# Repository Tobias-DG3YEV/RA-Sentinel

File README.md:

# Project RA-Sentinel - a Radio Access Sentinel
FPGA-based Radio Receiver for securing WiFi and other access points against hacking attacks.

RA-Sentinel is an open-source project focused on creating a cost-effective, small, and low-power wideband radio receiver device that employs an FPGA to automatically detect malicious attacks on WiFi access points, such as Man in the Middle and Denial of Service attacks. By monitoring any WiFi cell, the device enhances internet safety for everyday users.
The device features low-cost receive-only chips that digitize 40 MHz of the WiFi radio spectrum at 2.4 GHz. An FPGA extracts relevant properties from demodulated and decoded packets in real-time without storage. These properties are then processed by a neural network, also implemented on the FPGA, to determine if the traffic is genuine or an attack.

The project was later extended with a directional 4-channel RF front end (RASRF2400WBMC) that adds Angle of Arrival (AoA) estimation, see the Sub Projects section below.

## Funding
<p align="center">
  
  &nbsp;&nbsp;
  
</p>

**RA-Sentinel (main project)**

This project was funded through the [NGI0 Entrust](https://nlnet.nl/entrust) Fund, a fund established by [NLnet](https://nlnet.nl/) with financial support from the European Commission's [Next Generation Internet](https://ngi.eu/) programme, under the aegis of [DG Communications Networks, Content and Technology](https://commission.europa.eu/about-european-commission/departments-and-executive-agencies/communications-networks-content-and-technology_en) under grant agreement No 101069594.

**RASRF2400WBMC (directional / AoA extension)**

This sub-project was funded through the [NGI0 Commons Fund](https://nlnet.nl/commonsfund), a fund established by [NLnet](https://nlnet.nl/) with financial support from the European Commission's [Next Generation Internet](https://ngi.eu/) programme, under the aegis of [DG Communications Networks, Content and Technology](https://commission.europa.eu/about-european-commission/departments-and-executive-agencies/communications-networks-content-and-technology_en) under grant agreement No [101135429](https://cordis.europa.eu/project/id/101135429). Additional funding is made available by the [Swiss State Secretariat for Education, Research and Innovation](https://www.sbfi.admin.ch/sbfi/en/home.html) (SERI).

---

## Latest Updates 

| Date       | Change                                                                                                                                                                                          | Link                                                                                        |
| ---------- | ----------------------------------------------------------------------------------------------------------------------------------------------------------------------------------------------- | ------------------------------------------------------------------------------------------- |
| 2026-10-08 | Four-channel receiver: angle-of-arrival polar display, real-time phase comparison, IQ snapshot capture to a PC over gigabit Ethernet. FPGA1 now free of Xilinx IP (openCMUL, openCDIV, openFFT) | [/Documentation/iq_capture](./Documentation/iq_capture/README.md)                           |
| 2026-09-30 | RASBB Revision C manufacturing started                                                                                                                                                          |                                                                                             |
| 2026-07-24 | RASPMO - 4ch Spectrum Monitor/Phase analysis                                                                                                                                                    | [/RASPMO](./RASPMO)                                                                         |
| 2026-06-30 | RASANT2400 - 2.4 GHz antenna for RF front ends                                                                                                                                                  | [/RASANT2400](./RASANT2400)                                                                 |
| 2026-04-15 | RASRF2400WBMC - directional 4-channel RF front end for Angle-of-Arrival estimation                                                                                                              | [/RASRF2400WBMC](./RASRF2400WBMC/README.md)                                                 |
| 2025-12-15 | RASBB_ECU firmware - adds UPNP discovery over Ethernet and a system configuration web page                                                                                                      | [/RASBB/Software/RASBB_ECU](./RASBB/Software/RASBB_ECU)                                     |
| 2025-02-23 | First boards of RASBB and RASRF2400WB received; bring-up ongoing                                                                                                                                | [RASBB README](./RASBB/README.md) &nbsp;\|&nbsp; [Findings Rev A](./RASBB/Findings_RevA.md) |

---

## System Architecture

---
## Hardware

The hardware is a wideband SDR receiver that receives at least one complete WiFi Channel on the 2.4GHz ISM band with high resolution (12 Bits) to be able to detect smallest anomalies in a transmitted signal. The initial evaluation hardware consists of a Downcoverter/Transceiver Chip for 2.4GHz which is widely used in older WiFi Access Points (MAX2831). This is followed by a 12 Bit ADC (Texas Instruments ADC3222) which converts a 40MHz window of the 2.4GHZ radio spectrum into a 4 x 240 Bit/s LVDS streams (960kBit/s total) into a XILNIX/AMD Artix7 FPGA sitting on a evaluation board made by QMTECH. 

Based on the experience collected with first prototype, we designed a new SDR prototype. Two boards of the RASBB and the RASRF2400 have arrived on 23rd. Feb. 2025
Testing and bringing up is now ongoing. First results and findings can be found in the corresponding [Findings_RevA.md](./RASBB/Findings_RevA.md) documents.

### Boards

| Board | Description | Location |
|---|---|---|
| **RFFE2400WB** | 2.4 GHz PMOD-connected RF front-end evaluation board (used with QM-Tech Artix-7) | [/RFFE2400WB](./RFFE2400WB) |
| **RASBB** | Base-band board with STM32 ECU, web config, Ethernet/UPNP | [/RASBB](./RASBB) |
| **RASRF2400WB** | Wideband 2.4 GHz RF front end (production variant) | [/RASRF2400WB](./RASRF2400WB) |
| **RASRF2400WBMC** | Directional 4-channel phase-coherent front end (AoA) - *new sub-project* | [/RASRF2400WBMC](./RASRF2400WBMC) |
| **RASANT2400** | 2.4 GHz antenna for RF front ends| [/RASANT2400](./RASANT2400) |

*Picture 1: First RA-Sentinel prototype based on the QM-Tech Artix-7 board and a newly designed RF front end connected via PMOD.*

*Picture 2: RA-Sentinel prototype Revision A with RF front-end board RASRF2400WB.*

FPGA development board reference: <https://de.aliexpress.com/item/1005006473783593.html>

---

## Software / Firmware

The vast majority of the code will be written in Verilog and run on the FPGA. There is also now a firmware for the RASBB_ECU (Embedded Control Unit) and a"house keeping unit" microcontroller (STM32C031) which programms and controlling the frontend chips. The RASBB_ECU provides the interconnectivity. with other systems (alarm forwarding) and the web configuration interface. This firmware is written in C. 

The firmware for the RASBB_ECU can be found The firmware for the RASBB_ECU can be found [here](./RASBB/Software/RASBB_ECU). 

The RASBB_ECU Firmware for the onboard STM32 provides a versatile configuration interface with GUI that allows to show statistics and maybe UDP for analytic packets transfer and secure TCP/IP configuration over Ethernet.
To access this, enter the IP of the RAS into your local browser like http://192.168.0.2:4842/. The IP can be easily found via network environment because the RAS supports UPNP over ethernet.

All original software/firmware code written for this project is licensed under the GNU General Public License 3.0 (Only).

A suspected WiFi node can be

* Tracked: Monitored by relative signal strength and later with additional direction. These values are forwarded to an IDS host that can combine this information with additional data retrieved from different RAS or other network monitoring systems.
* Tagged: Marked for internal memory, moving up in watch list.
* Fingerprinted: Raw IQ data of the frame start is forwarded to a fingerprinting algorithm.

**UPNP support**

To ease the installation process, the RAS can be connected to any ethernet based LAN that provides an IPv4 DHCP server. Through the UPNP support, the RAS is easy to find in any network browser of Windows, Linux and Mac etc. 

---

## Sub Projects / Project Steps

The first step on this project was to have a reliable hardware basis. Initially I planned to have at least 40 Megasamples and with this 20 MHz bandwidth which is sufficient to capture the headers and the most common bandwidths used on 2.4 GHz WiFi (802.11a, b, g) communications channel. But because 802.11n also defines the possibility to use 40 MHz bandwidth, I wanted the possibility to cover the complete possible channel bandwidth. This has been achieved with the first prototype hardware and proved with the sub-project RASM2400, Radio Access Spectrum Monitor for 2400 MHz. The directional variant, RASRF2400WBMC, extends this base with multi-channel phase-coherent reception so the same signal can be received across several antennas and the direction of an attack can be estimated. You can find all sub-project details below.

### Sub project: RASRF2400WBMC - Directional RF Front End

The **RASRF2400WBMC** is a 4-channel, phase-coherent 2.4 GHz RF front-end board that extends RA-Sentinel with **Angle of Arrival (AoA)** estimation. By receiving the same signal across four spatially separated antennas, the system can estimate the physical direction of a detected attack - enabling threat localization for jamming, spoofing, and unauthorized events.

The board connects to the existing RASBB via the PCIe connector and requires no hardware changes to the base-band board.

See **[RASRF2400WBMC/README.md](./RASRF2400WBMC/README.md)** for full details.

### Sub project: RASM2400 - a spectrum monitor

RASM2400 stands for Radio Access Spectrum Monitor operationg on 2400MHZ. It offers a visual spectrum analyzer design that runs on the evaluation hardware set of RA-Sentinel the Artix7 XC7A100T Wukong board and the RFFE2400 front end board.
It shall proove that a 40MHz wide radio spectrum can be received and transported into the FPGA. Further, this project may already be usable for first RF forensics. Feel free to download all the stuff and build an RASM by yourself.

The following diagram shows the system architecture of the RASM2400.

The output of the HDMI port of the QMTECH Wukong board.

Watch a short demonstration on Youtube by clicking on the thumbnail below.

#### Software

In this repository you'll find also all software paerts needed to get the project up and running.

**/RASM2400_Verilog**

This folder contains the Verilog source files as well as a ready to program bit stream file. 

**/RASM2400_HKU**

Here you find the firmware for the RF board housekeeping unit. It does not do much a the moment but initializing the Downconverter MAX2831 and the ADC3222. It is planned to receive commands via I2C to change basic parameters wil center frequency, sensitivity and AGC characteristics. This project can be compiled with arm-gcc or with the free available and Eclipse based development environment (IDE) from ST called "STM32CubeIDE". You can download this IDE from ST.com [https://www.st.com/en/development-tools/stm32cubeide.html]

**/RASPMO**

Radio Access Spectrum Monitor with HDMI Output. A firmware project for the analog processing FPGA (U10).
THis shows all four spectra of all four channels of the RASRF2400BMC front end on the HDMI output at 1080p60 resolution. It also can overlay a polar indicator that gices an coarse indication where the signal is comming from. 

#### Project update 13th Oct. 2024

The target of the next Milestone #2 was the „Identification and isolation of appropriate software components“ and also to „Additionally apply modifications to the openOFDMmodule to get extra meta data out of the frame demodulator to have a wider data basis for the later fingerprinting process.“

In the following points I describe how I achieved each step of this Milestone.

**1. compile/synthesize openWiFi on the target FPGA**

The code of openWiFi has been successfully ported from the project GitHub site [1] to the evaluation setup that I have designed and set up in the first Milestone. After gluing together the ADC LVDS deserializer block inside the FPGA with the parallel input of the openOFDM core, got rid of several timing constraint issues, I finally achieved to decode a WiFi Frame coming from an arbitrary signal generator. To accomplish this target, the code needed to be isolated from the original open WiFi demo project code. This original demo was based on SDR evaluation boards relying all on the AMD ZYNQ FPGA-ARM chip family. This family provides an FPGA part and an integrated ARM micro processor to which all communication of the FPGA part is connected to. Data from and to the integrated processor is exchanged through a common memory bus. This however is not working with my design idea which is based on a more powerful FPGA with an external ARM co-processor. I tried extracting the needed HDL (Verilog) parts and make this code running stand-alone. Finally I came the conclusion that only the project „openOFDM“ needs to be ported to my RA-Sentinel project hardware because the network layer and the transmit part implemented in openWiFi is not really needed by the RA-Sentinel project because there is no need in routing real data back and forth to a network. We are only interested in the lowest layer of a WiFi frame and its analog characteristics, not the routing of packets and also not in the frame containing payload as such.

First I adapted the test-bench provided in [2] for the Vivado simulation environment. To be able to simulate the complete RA-Sentinel hardware, I created a LVDS emulator that can stream artificial synthesized and recorded  RF data coming originally from the TI ADC 3221. After providing recorded RF data via this LVDS simulator and generating a appropriate, to the ADC phase-locked master clock of 100MHz to the openOFDM core and (see top_tb.v), this setup was able to decode a complete 802.11a/g frame in the AMD Vivado simulator. It took me quite some fiddling and playing with timings and implementation settings of the tool-chain to finally get it running properly on my own hardware. (AMD Artix7 development board my QM-Tech and my 2.4GHz ADC board designed in Milestone 1)

**2. Strip down openWiFi and open OFDM to the receive part**

First this was regarded as an easy task but as deeper I dived into the code  by the original author of the two projects, the more I realized the code provides almost no comments and wire and register definitions are quite ambiguous and non-intuitive. In my opinion the code needed desperately a rework to be better understandable which would also lead to a lower learning curve for others also trying to implement and adapt the existing code base to their needs. Two major things I tried improving with my fork of openOFDM: The introduction of directional prefixes for module ports. I have seen such in the code of another NLnet founded guy called Dan Nissselquist. Adding the prefix  „i_“ to  input ports (defined as wires/registers in Verilog) and „o_“ to the port definition makes it IMHO much easier when browsing through the code, allowing to instantly realize which wire or register is being exported from this current module and which is only a local element. I added these prefixes all over the code of openOFDM. See my fork of openOFDM on GitHub [1] for details. The next thing I found hard to understand, was the use of the ever repeating word „sample“ for all data along the signal path, from the input of the openOFDM core (ADC base-band data) up to near the exit (decoded data bytes). As there is a switch from time domain (endless sample stream) into frequency domain (blocks of 64 frequency bands) in the module „sync_long“, I changed the name of all wires and registers after this module and renamed them into „spectrum“.  Also some comments were added to clarify what a wire or register is doing at a certain point. This work is not yet regarded as being completed. Each time I dig into the original code, I will add comments and try to make the code more „barrier free“.

**3. Create a new fork of openOFDM**

This has been done and the new fork of openOFDm can be found here:

[1] https://github.com/Tobias-DG3YEV/openofdm

It contains comments and my code changes proposed earlier in this document.

**4. Try adding additional meta date stubs**

As I tried figuring out which meta data could be used to distinguish between  genuine transmitting device and a counterfeit device, I found an article at mathworks.com [3] reporting that they proved finding counterfeit, evil twins of a WiFi Access Point by feeding the raw sampled channel data of a transmission into a ML algorithm. For this purpose they followed a kind of a brute force approach by taking all samples of a received frame into account and fed into a ML algorithm. Even the smallest frame like an information or flow control frame that is only 100uS of duration will produce 16kBytes of data which is rather huge. This amount of data may be processable - if the SDR is directly connected to a powerful computer with multiple cores etc. The project RA-Sentinel does not follow this kind of big processing power approach. Amplitude, phase and frequency change due to several effects during the transmission of a frame, but all of these changes always result in a phase shift. So I thought, in  the first attempt identifying a WiFi transmitting device by characterizing (or say learning) the phase deviation over time may be sufficient. Because the RF receiver front end of the RA-Sentinel project has a low noise and high stability master clock (a 40MHz TXCO by Abracom) that is multiple times more accurate that standard commercial WiFi transmitters, I hope that a small amount of phase shift data received in the beginning of a WiFi frame may be enough to clearly identify counterfeit devices. 

**5. Redefine a new simplified interface to access meta parameters**

One thing I have learned throughout the project progress so far, is that even many may say that an FPGA is one of the most versatile digital programmable devices available today, allowing the implementation of any kind of parallel and sequential tasks up to integration of soft-core processors the fact is that all this integrated logic leads to a rather time consuming iterative development process. To optimize WiFi data reception on one side and to interpret and forward meta data on the other side all inside the FPGA leads to an extremely slow and challenging development process. For the analysis of meta data, an external, traditional single chip microprocessor running straight C/C++ code,  offers much more opportunities and most importantly, allows much a faster  development progress. Bit for that, I need a fast and reliable interconnection between the FPGA and the micro processor.

I identified and implemented two interfaces which allow to access 

The first interface I implemented into the FPGA was the SPI slave interface. This interface allows reading and writing 32 wide registers inside the FPGA by an external micro controller (in this case, I use a STM32H743 Cortex-M7)

The SPI interface allows access to the following parameters:

- Receiver characteristics like receiver center frequency, gain, power threshold, max. error rate etc.

- reading current receiver parameters like noise level, signal to noise ratio etc.

Further I needed an interface that is capable transferring header and  metadata that is produced with each WiFi 802.11 frame received to my  external ARM processor. As I cannot foresee at this point in the project how much meta data is needed to distinctly identify a sender hardware of a frame, I was looking for a method to reliably transport greater chunks of data from the FPGA directly into the memory of the external micro-controller without code intervention. Hence, I started evaluating the possibilities based on the peripheral capabilities of the STM32 device family.  After I had invested some effort into research and experiments, I found that SPI especially in a 4-Bit configuration might feasible as it is able transporting 25MByte/s. But the digital camera interface (DCMI) that many of those top range micro-controllers provide, offer 8 Bit parallel data transfer directly into the controller’s memory via DMA at a maximum rate of 80MBytes/s.

So the next step was to design a logic circuit into the FPGA that can mimic the signaling of a digital camera module with DCMI interface. This has been implemented on both sides, the FPGA in Verilog Code and on the STM32H7 in C language. 

The received 802.11 frame info packet that is streamed upon each complete frame reception has the following format:

---

**Resources:**

[1] https://github.com/open-sdr/openWiFi-hw/

[2] https://github.com/Tobias-DG3YEV/openofdm

[3] https://de.mathworks.com/help/comm/ug/design-a-deep-neural-network-with-simulated-data-to-detect-wlan-router-impersonation.html

Project Maintainer: Tobias Weber, Mina Daneshpajouh

Last updated: 17. May. 2026

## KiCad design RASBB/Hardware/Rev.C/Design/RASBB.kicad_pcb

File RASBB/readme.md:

# RA-Sentinel System Overview

The **RA-Sentinel** system consists of two main boards that work together to enable high-performance RF signal reception, digitization, and processing.

## RA-Sentinel Radio Front-End Board (RASRF)
The **RASRF** board is responsible for receiving and conditioning, and digitizing RF signals before transmitting them to the baseband processor.
 - The antenna is connected through a Balun to an RF front-end transceiver, which performs signal reception, downconversion, and filtering.
 - The downconverted signal is then conditioned using a driver circuit optimized for impedance matching and signal integrity.
 - A high-speed 12-bit ADC samples a 40 MHz portion of the 2.4 GHz radio spectrum, converting it into a 960 Mbit/s data stream (2 channels: I+Q, 12-bit each @ 40 
   MSPS). 
 - The digitized data is transmitted over a PCIe interface to the RASBB board for baseband processing.

## RA-Sentinel Baseband Board (RASBB)
The **RASBB** board processes the received digital RF data and manages higher-layer communication.
 - It performs baseband signal processing, extracting relevant information from the digitized RF data.
 - It transitions the processed data from OSI Layer 1 (Physical) to OSI Layer 2 (Data Link) for further communication and protocol handling.
 - The board integrates additional processing units and interfaces for system-level control, data management, and external communication.

Together, the **RASRF** and **RASBB** boards create a scalable, high-performance platform for RF signal acquisition and real-time processing.

Below is the block diagram illustrating the architecture of both boards and their interconnections:

## The hardware

The PCB of the RASBB is made of an FR4 eight-layer PCB, which contains several processing units, sensors, and radio and wired interfaces.
Below is an list of its features:

- Two Artix-7 FPGAs with 100k Logic Elements each
- 4 Gigabit (512MB with 16-bit access) Low Voltage DDR3 RAM
- STM32H7 high-performance (up to 480MHz) ARM Cortex-M7 microcontroller
- x8 PCI Express slot, designed to be compatible with PCI standards
- HDMI port, with video generated in FPGA 1
- 40-bit (32+8) inter-processor communication bridge (accessible by external logic analyzers)
- Two separately usable 16M Flash chips for FPGA configuration, accessible by both FPGA and STM32
- Temperature and humidity sensor for physical environment supervision
- Audio DAC with a 1W output amplifier (for alarm and voice output)
- Audio ADC for capacitive microphone connection (for acoustic environment surveillance)
- Open-collector 30V/1A capable switching output (for alarming devices)
- USB-C port with virtual COM port support for debugging and updates
- 2.4GHz LoRaWAN™ modem chip for robust alarm distribution
- 100Mbit/s Ethernet port connected to the STM32H7 MCU
- 1Gbit/s Ethernet port connected to FPGA 2
- Power over Ethernet (PoE) Type 1 with a maximum power of 13W
- LEDs for indication
- Configuration button
- FPGAs and STM32 accessible through JTAG port

*The RA-Sentinel Baseband Board design will fit into a 100mm extrusion enclosure. Hardware designed by **Mina Daneshpajouh**.*

RASBB Rev A (Top View)

RASBB Rev B (Bottom View)

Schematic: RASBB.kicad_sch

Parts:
C1, C2: 1uF; C_0402_1005Metric; Mfr. Part # 0402X105M160CT; LCSC Part # C3889771
C270: 100nF; C_0402_1005Metric; Mfr. Part # 0402B104K500CT; LCSC Part # C152814
C271, C272: 2200pF; C_0402_1005Metric; Mfr. Part # 0402B222K500NT; LCSC Part # C1531
J20: PWM_DAC_OUT; PinHeader_1x02_P2.54mm_Vertical; Mfr. Part # PZ254V-11-02P; LCSC Part # C492401
R1, R2, R3, R4, R6, R7, R8, R11, R12, R13, R14, R15, R16, R22: 49.9; R_0402_1005Metric; Mfr. Part # RMCF0402FT49R9; LCSC Part # C4229190
R9, R10: 4K7; R_0402_1005Metric; Mfr. Part # WR04X4701FTL; LCSC Part # C163826
R17, R18, R19, R20, R23, R24: 22; R_0402_1005Metric; Mfr. Part # WR04X22R0FTL; LCSC Part # C163821
R21, R168, R169, R170, R171, R172, R173, R174, R175, R176, R177, R178, R179, R180, R181, R182, R183, R184: 100; R_0402_1005Metric; Mfr. Part # WR04X1000FTL; LCSC Part # C163808
R150: 0; R_0603_1608Metric; Mfr. Part # RC0603JR-070RL; LCSC Part # C95177
R151, R195, R200, R201: 10K; R_0603_1608Metric; Mfr. Part # 0603WAF1002T5E; LCSC Part # C25804
SW1, SW2: 435451019820; Mfr. Part # 435451019820
TP6, TP7, TP8, TP9, TP10, TP11, TP12, TP13, TP14, TP15, TP16, TP17, TP18, TP19, TP20, TP21, TP22: TestPoint; TestPoint_Pad_D1.0mm; not fitted
U5: TLV9001DBVR; SOT-23-5; Mfr. Part # TLV9001QDBVRQ1; LCSC Part # C19632595

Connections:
/Audio_IN-OUT/3V3: C270.1, R9.2, R10.2, R200.2, R201.2, U5.5 (V+); also elsewhere on the board
/Audio_IN-OUT/Audio_IN: R21.2; also elsewhere on the board
/Audio_IN-OUT/LM386_INP: C2.2; also elsewhere on the board
/CS_FLASH_uC: TP18.1 (1_1); also elsewhere on the board
/Config-SPI FLASH/MUX_EN1: TP19.1 (1_1); also elsewhere on the board
/Config-SPI FLASH/MUX_EN2: TP20.1 (1_1); also elsewhere on the board
/Config-SPI FLASH/SCK_FLASH_FPGA2: R6.1; also elsewhere on the board
/Config-SPI FLASH/SCK_Flash_FPGA1: R1.2; also elsewhere on the board
/Config-SPI FLASH/SI_FLASH_FPGA2: R7.1; also elsewhere on the board
/Config-SPI FLASH/SI_Flash_FPGA1: R2.2; also elsewhere on the board
/Config-SPI FLASH/SO_FLASH_FPGA2: R8.1; also elsewhere on the board
/Config-SPI FLASH/SO_Flash_FPGA1: R4.2; also elsewhere on the board
/Config-SPI FLASH/SWITCH_FLASH_1: TP22.1 (1_1); also elsewhere on the board
/Config-SPI FLASH/SWITCH_FLASH_2: TP21.1 (1_1); also elsewhere on the board
/Ethernet_uC/RMII_CRS_DV: R20.1; also elsewhere on the board
/Ethernet_uC/RMII_REFCLK: R18.1; also elsewhere on the board
/Ethernet_uC/RMII_RXD0: R23.1; also elsewhere on the board
/Ethernet_uC/RMII_RXD1: R24.1; also elsewhere on the board
/Ethernet_uC/RMII_TXD0: R19.1; also elsewhere on the board
/Ethernet_uC/RMII_TXD1: R17.1; also elsewhere on the board
/FPGA1_RESET: SW1.4; also elsewhere on the board
/FPGA2_RESET: SW2.4; also elsewhere on the board
/FPGA-01/FPGA1_CLK: R1.1; also elsewhere on the board
/FPGA-01/FPGA1_MISO: R4.1; also elsewhere on the board
/FPGA-01/FPGA1_MOSI: R2.1; also elsewhere on the board
/FPGA-02/F2_B35_J2: R195.1; also elsewhere on the board
/PCIE/PCIE_MISO: R12.1; also elsewhere on the board
/PCIE/PCIE_MOSI: R3.1; also elsewhere on the board
/PCIE/PCIE_SCK: R11.1; also elsewhere on the board
/PCIE/RX0_N: R168.1; also elsewhere on the board
/PCIE/RX0_P: R168.2; also elsewhere on the board
/PCIE/RX1_N: R169.1; also elsewhere on the board
/PCIE/RX1_P: R169.2; also elsewhere on the board
/PCIE/RX2_N: R170.1; also elsewhere on the board
/PCIE/RX2_P: R170.2; also elsewhere on the board
/PCIE/RX3_N: R171.1; also elsewhere on the board
/PCIE/RX3_P: R171.2; also elsewhere on the board
/PCIE/RX4_N: R172.1; also elsewhere on the board
/PCIE/RX4_P: R172.2; also elsewhere on the board
/PCIE/RX5_N: R173.1; also elsewhere on the board
/PCIE/RX5_P: R173.2; also elsewhere on the board
/PCIE/RX6_N: R174.1; also elsewhere on the board
/PCIE/RX6_P: R174.2; also elsewhere on the board
/PCIE/RX7_N: R175.1; also elsewhere on the board
/PCIE/RX7_P: R175.2; also elsewhere on the board
/PCIE/RX8_N: R176.1; also elsewhere on the board
/PCIE/RX8_P: R176.2; also elsewhere on the board
/PCIE/RX9_N: R177.1; also elsewhere on the board
/PCIE/RX9_P: R177.2; also elsewhere on the board
/PCIE/RX10_N: R178.1; also elsewhere on the board
/PCIE/RX10_P: R178.2; also elsewhere on the board
/PCIE/RX11_N: R179.1; also elsewhere on the board
/PCIE/RX11_P: R179.2; also elsewhere on the board
/PCIE/RX12_N: R180.1; also elsewhere on the board
/PCIE/RX12_P: R180.2; also elsewhere on the board
/PCIE/RX13_N: R181.1; also elsewhere on the board
/PCIE/RX13_P: R181.2; also elsewhere on the board
/PCIE/RX14_N: R182.1; also elsewhere on the board
/PCIE/RX14_P: R182.2; also elsewhere on the board
/PCIE/RX15_N: R183.1; also elsewhere on the board
/PCIE/RX15_P: R183.2; also elsewhere on the board
/PCIE/RX16_N: R184.1; also elsewhere on the board
/PCIE/RX16_P: R184.2; also elsewhere on the board
/PCIE/SMCLK: R10.1; also elsewhere on the board
/PCIE/SMDAT: R9.1; also elsewhere on the board
/RF_Transceiver/BUSY_LORA_G: TP13.1 (1_1); also elsewhere on the board
/RF_Transceiver/DIO1_LORA_G: TP12.1 (1_1); also elsewhere on the board
/RF_Transceiver/DIO2_LORA_G: TP11.1 (1_1); also elsewhere on the board
/RF_Transceiver/DIO3_LORA_G: TP10.1 (1_1); also elsewhere on the board
/RF_Transceiver/NRST_LORA_G: TP14.1 (1_1); also elsewhere on the board
/RF_Transceiver/SPI_MISO_LORA_G: R22.2; also elsewhere on the board
/RF_Transceiver/SPI_MOSI_LORA_G: R16.2, TP7.1 (1_1); also elsewhere on the board
/RF_Transceiver/SPI_NSS_LORA_G: TP9.1 (1_1); also elsewhere on the board
/RF_Transceiver/SPI_SCK_LORA_G: R15.2, TP8.1 (1_1); also elsewhere on the board
/SCK_FLASH_FPGA2: R6.2; also elsewhere on the board
/SCK_FLASH_uC: R13.1, TP17.1 (1_1); also elsewhere on the board
/SI_FLASH_FPGA2: R7.2; also elsewhere on the board
/SI_FLASH_uC: R14.1, TP16.1 (1_1); also elsewhere on the board
/SO_FLASH_FPGA2: R8.2; also elsewhere on the board
/SO_FLASH_uC: TP15.1 (1_1); also elsewhere on the board
/uController/ADC1_IN5: C1.1; also elsewhere on the board
/uController/uC_DAC2_OUT2: C2.1; also elsewhere on the board
/uController/uC_ETH_CRS_DV: R20.2; also elsewhere on the board
/uController/uC_ETH_REF_CLK: R18.2; also elsewhere on the board
/uController/uC_ETH_RXD0: R23.2; also elsewhere on the board
/uController/uC_ETH_RXD1: R24.2; also elsewhere on the board
/uController/uC_ETH_TXD0: R19.2; also elsewhere on the board
/uController/uC_ETH_TXD1: R17.2; also elsewhere on the board
/uController/uC_SPI2_MISO: R22.1, TP6.1 (1_1); also elsewhere on the board
/uController/uC_SPI2_MOSI: R16.1; also elsewhere on the board
/uController/uC_SPI2_SCK: R15.1; also elsewhere on the board
/uController/uC_SPI3_MISO: R3.2; also elsewhere on the board
/uController/uC_SPI3_MOSI: R12.2; also elsewhere on the board
/uController/uC_SPI3_SCK: R11.2; also elsewhere on the board
/uController/uC_SPI4_MOSI: R14.2; also elsewhere on the board
/uController/uC_SPI4_SCK: R13.2; also elsewhere on the board
GND: C270.2, C271.2, C272.2, J20.1, SW1.2, SW1.3, SW1.5 (GND), SW2.2, SW2.3, SW2.5 (GND), U5.2 (V-); also elsewhere on the board
unnamed: C1.2, R21.1
unnamed: C272.1, R151.2, R195.2
unnamed: J20.2, R150.1
unnamed: R200.1, SW1.1
unnamed: R201.1, SW2.1
unnamed: C271.1, R151.1, U5.3 (+)
unnamed: R150.2, U5.1, U5.4 (-)

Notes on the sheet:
f3dB:5Hz

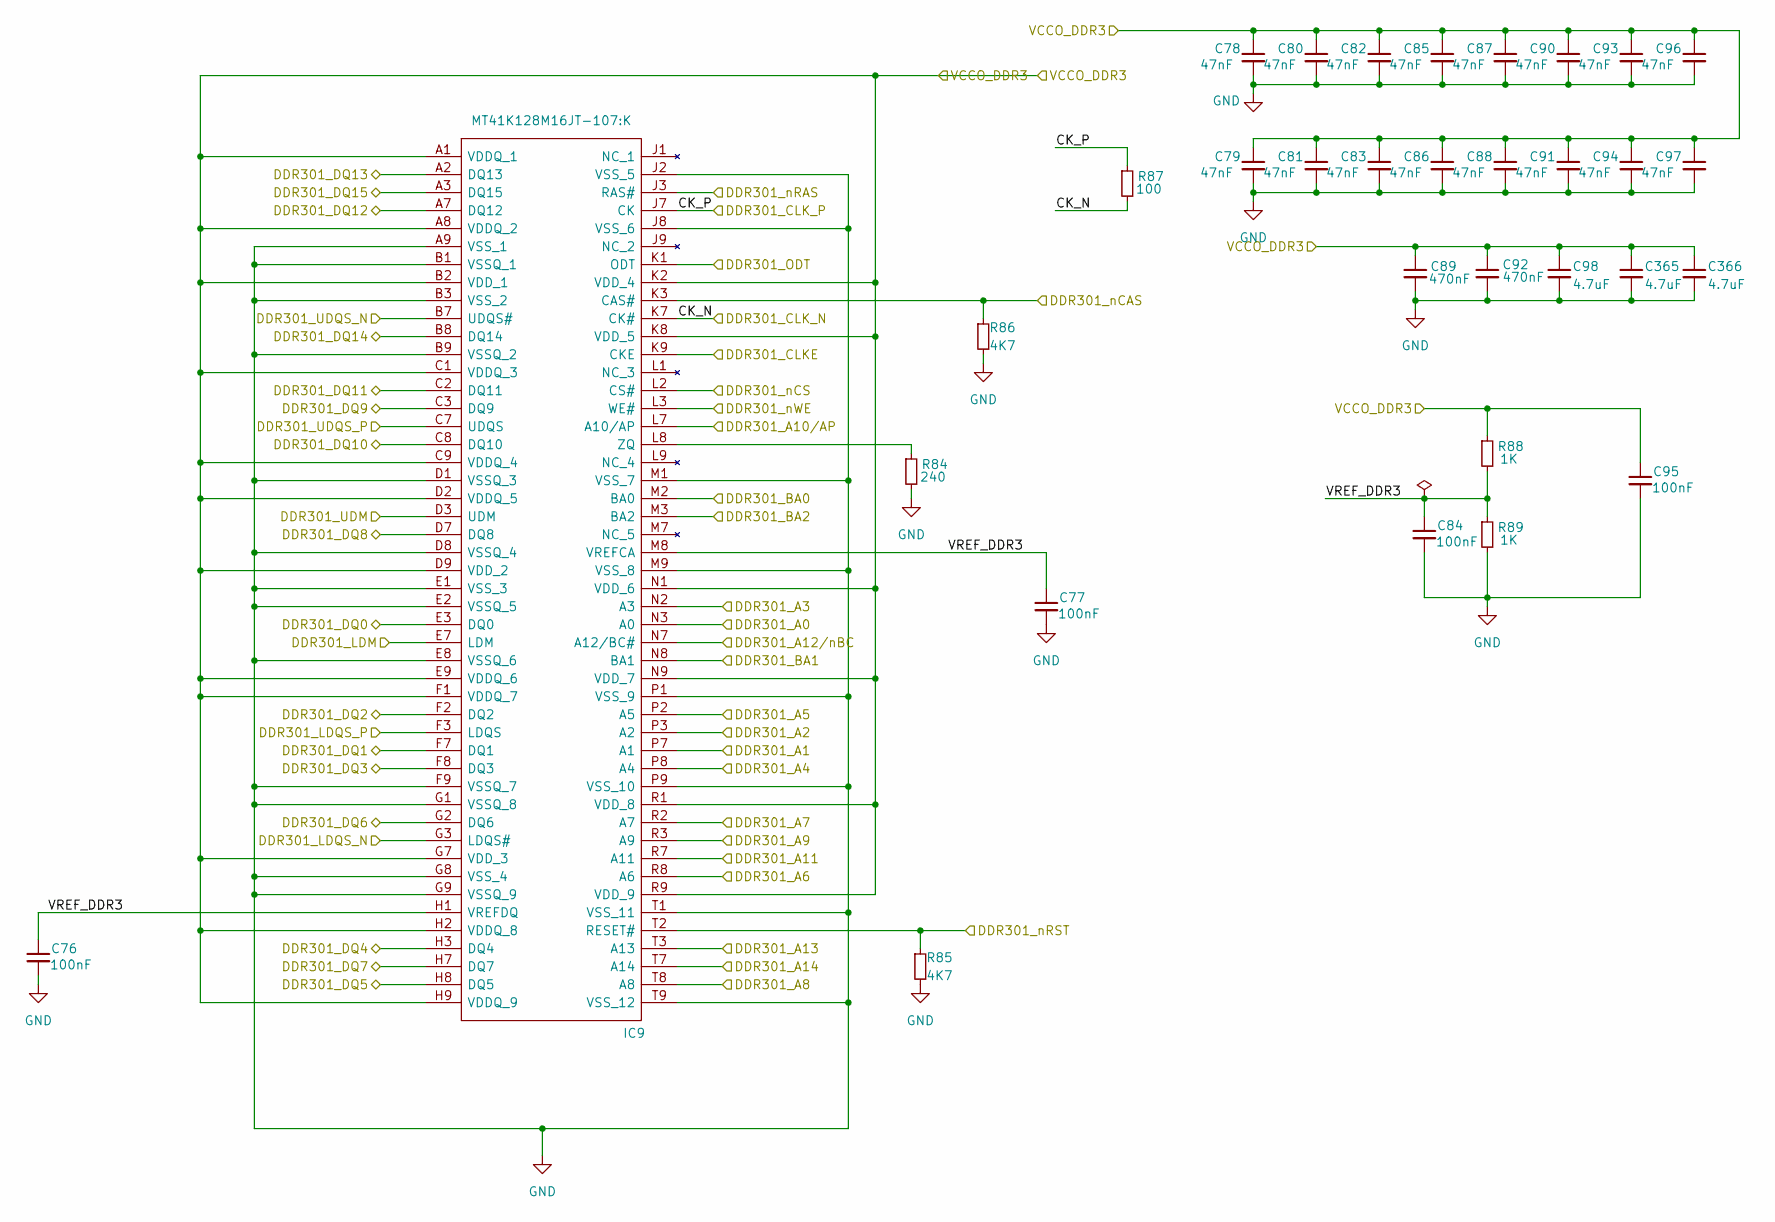
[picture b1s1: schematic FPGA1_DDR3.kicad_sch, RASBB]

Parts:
C76, C77, C84, C95: 100nF; C_0402_1005Metric; Mfr. Part # 0402B104K500CT; LCSC Part # C152814
C78, C79, C80, C81, C82, C83, C85, C86, C87, C88, C90, C91, C93, C94, C96, C97: 47nF; C_0402_1005Metric; Mfr. Part # C0402C473J8RAC7867; LCSC Part # C2178375
C89, C92: 470nF; C_0402_1005Metric; Mfr. Part # GRM155R71C474KE01D; LCSC Part # C471404
C98, C365, C366: 4.7uF; C_0603_1608Metric; Mfr. Part # GMK107BBJ475KA-T; LCSC Part # C7281848
IC9: MT41K128M16JT-107:K; BGA96C80P9X16_800X1400X120; Mfr. Part # MT41K128M16JT-107:K; LCSC Part # C2841151
R84: 240; R_0402_1005Metric; Mfr. Part # RT0402BRE07240RL; LCSC Part # C728568
R85, R86: 4K7; R_0402_1005Metric; Mfr. Part # WR04X4701FTL; LCSC Part # C163826
R87: 100; R_0402_1005Metric; Mfr. Part # WR04X1000FTL; LCSC Part # C163808
R88, R89: 1K; R_0402_1005Metric; Mfr. Part # MR04X1001FTL; LCSC Part # C327796

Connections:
/DDR3-01/CK_N: IC9.K7 (CK#), R87.2; also elsewhere on the board
/DDR3-01/CK_P: IC9.J7 (CK), R87.1; also elsewhere on the board
/DDR3-01/DDR301_A0: IC9.N3 (A0); also elsewhere on the board
/DDR3-01/DDR301_A1: IC9.P7 (A1); also elsewhere on the board
/DDR3-01/DDR301_A2: IC9.P3 (A2); also elsewhere on the board
/DDR3-01/DDR301_A3: IC9.N2 (A3); also elsewhere on the board
/DDR3-01/DDR301_A4: IC9.P8 (A4); also elsewhere on the board
/DDR3-01/DDR301_A5: IC9.P2 (A5); also elsewhere on the board
/DDR3-01/DDR301_A6: IC9.R8 (A6); also elsewhere on the board
/DDR3-01/DDR301_A7: IC9.R2 (A7); also elsewhere on the board
/DDR3-01/DDR301_A8: IC9.T8 (A8); also elsewhere on the board
/DDR3-01/DDR301_A9: IC9.R3 (A9); also elsewhere on the board
/DDR3-01/DDR301_A10/AP: IC9.L7 (A10/AP); also elsewhere on the board
/DDR3-01/DDR301_A11: IC9.R7 (A11); also elsewhere on the board
/DDR3-01/DDR301_A12/nBC: IC9.N7 (A12/BC#); also elsewhere on the board
/DDR3-01/DDR301_A13: IC9.T3 (A13); also elsewhere on the board
/DDR3-01/DDR301_A14: IC9.T7 (A14); also elsewhere on the board
/DDR3-01/DDR301_BA0: IC9.M2 (BA0); also elsewhere on the board
/DDR3-01/DDR301_BA1: IC9.N8 (BA1); also elsewhere on the board
/DDR3-01/DDR301_BA2: IC9.M3 (BA2); also elsewhere on the board
/DDR3-01/DDR301_CLKE: IC9.K9 (CKE); also elsewhere on the board
/DDR3-01/DDR301_DQ0: IC9.E3 (DQ0); also elsewhere on the board
/DDR3-01/DDR301_DQ1: IC9.F7 (DQ1); also elsewhere on the board
/DDR3-01/DDR301_DQ2: IC9.F2 (DQ2); also elsewhere on the board
/DDR3-01/DDR301_DQ3: IC9.F8 (DQ3); also elsewhere on the board
/DDR3-01/DDR301_DQ4: IC9.H3 (DQ4); also elsewhere on the board
/DDR3-01/DDR301_DQ5: IC9.H8 (DQ5); also elsewhere on the board
/DDR3-01/DDR301_DQ6: IC9.G2 (DQ6); also elsewhere on the board
/DDR3-01/DDR301_DQ7: IC9.H7 (DQ7); also elsewhere on the board
/DDR3-01/DDR301_DQ8: IC9.D7 (DQ8); also elsewhere on the board
/DDR3-01/DDR301_DQ9: IC9.C3 (DQ9); also elsewhere on the board
/DDR3-01/DDR301_DQ10: IC9.C8 (DQ10); also elsewhere on the board
/DDR3-01/DDR301_DQ11: IC9.C2 (DQ11); also elsewhere on the board
/DDR3-01/DDR301_DQ12: IC9.A7 (DQ12); also elsewhere on the board
/DDR3-01/DDR301_DQ13: IC9.A2 (DQ13); also elsewhere on the board
/DDR3-01/DDR301_DQ14: IC9.B8 (DQ14); also elsewhere on the board
/DDR3-01/DDR301_DQ15: IC9.A3 (DQ15); also elsewhere on the board
/DDR3-01/DDR301_LDM: IC9.E7 (LDM); also elsewhere on the board
/DDR3-01/DDR301_LDQS_N: IC9.G3 (LDQS#); also elsewhere on the board
/DDR3-01/DDR301_LDQS_P: IC9.F3 (LDQS); also elsewhere on the board
/DDR3-01/DDR301_ODT: IC9.K1 (ODT); also elsewhere on the board
/DDR3-01/DDR301_UDM: IC9.D3 (UDM); also elsewhere on the board
/DDR3-01/DDR301_UDQS_N: IC9.B7 (UDQS#); also elsewhere on the board
/DDR3-01/DDR301_UDQS_P: IC9.C7 (UDQS); also elsewhere on the board
/DDR3-01/DDR301_nCAS: IC9.K3 (CAS#), R86.1; also elsewhere on the board
/DDR3-01/DDR301_nCS: IC9.L2 (CS#); also elsewhere on the board
/DDR3-01/DDR301_nRAS: IC9.J3 (RAS#); also elsewhere on the board
/DDR3-01/DDR301_nRST: IC9.T2 (RESET#), R85.1; also elsewhere on the board
/DDR3-01/DDR301_nWE: IC9.L3 (WE#); also elsewhere on the board
/DDR3-01/VCCO_DDR3: C78.1, C79.1, C80.1, C81.1, C82.1, C83.1, C85.1, C86.1, C87.1, C88.1, C89.1, C90.1, C91.1, C92.1, C93.1, C94.1, C95.1, C96.1, C97.1, C98.1, C365.1, C366.1, IC9.A1 (VDDQ_1), IC9.A8 (VDDQ_2), IC9.B2 (VDD_1), IC9.C1 (VDDQ_3), IC9.C9 (VDDQ_4), IC9.D2 (VDDQ_5), IC9.D9 (VDD_2), IC9.E9 (VDDQ_6), IC9.F1 (VDDQ_7), IC9.G7 (VDD_3), IC9.H2 (VDDQ_8), IC9.H9 (VDDQ_9), IC9.K2 (VDD_4), IC9.K8 (VDD_5), IC9.N1 (VDD_6), IC9.N9 (VDD_7), IC9.R1 (VDD_8), IC9.R9 (VDD_9), R88.1; also elsewhere on the board
/DDR3-01/VREF_DDR3: C76.1, C77.1, C84.1, IC9.H1 (VREFDQ), IC9.M8 (VREFCA), R88.2, R89.1
GND: C76.2, C77.2, C78.2, C79.2, C80.2, C81.2, C82.2, C83.2, C84.2, C85.2, C86.2, C87.2, C88.2, C89.2, C90.2, C91.2, C92.2, C93.2, C94.2, C95.2, C96.2, C97.2, C98.2, C365.2, C366.2, IC9.A9 (VSS_1), IC9.B1 (VSSQ_1), IC9.B3 (VSS_2), IC9.B9 (VSSQ_2), IC9.D1 (VSSQ_3), IC9.D8 (VSSQ_4), IC9.E1 (VSS_3), IC9.E2 (VSSQ_5), IC9.E8 (VSSQ_6), IC9.F9 (VSSQ_7), IC9.G1 (VSSQ_8), IC9.G8 (VSS_4), IC9.G9 (VSSQ_9), IC9.J2 (VSS_5), IC9.J8 (VSS_6), IC9.M1 (VSS_7), IC9.M9 (VSS_8), IC9.P1 (VSS_9), IC9.P9 (VSS_10), IC9.T1 (VSS_11), IC9.T9 (VSS_12), R84.2, R85.2, R86.2, R89.2; also elsewhere on the board
unnamed: IC9.L8 (ZQ), R84.1

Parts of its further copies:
C99, C100, C107, C118: 100nF; C_0402_1005Metric; Mfr. Part # 0402B104K500CT; LCSC Part # C152814
C101, C102, C103, C104, C105, C106, C108, C109, C110, C111, C113, C114, C116, C117, C119, C120: 47nF; C_0402_1005Metric; Mfr. Part # C0402C473J8RAC7867; LCSC Part # C2178375
C112, C238: 470nF; C_0402_1005Metric; Mfr. Part # GRM155R71C474KE01D; LCSC Part # C471404
C115, C121, C186: 4.7uF; C_0603_1608Metric; Mfr. Part # GMK107BBJ475KA-T; LCSC Part # C7281848
IC10: MT41K128M16JT-107:K; BGA96C80P9X16_800X1400X120; Mfr. Part # MT41K128M16JT-107:K; LCSC Part # C2841151
R90: 240; R_0402_1005Metric; Mfr. Part # RT0402BRE07240RL; LCSC Part # C728568
R91, R92: 4K7; R_0402_1005Metric; Mfr. Part # WR04X4701FTL; LCSC Part # C163826
R93: 100; R_0402_1005Metric; Mfr. Part # WR04X1000FTL; LCSC Part # C163808
R94, R95: 1K; R_0402_1005Metric; Mfr. Part # MR04X1001FTL; LCSC Part # C327796

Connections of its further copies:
/DDR3-01/VCCO_DDR3: C101.1, C102.1, C103.1, C104.1, C105.1, C106.1, C108.1, C109.1, C110.1, C111.1, C112.1, C113.1, C114.1, C115.1, C116.1, C117.1, C118.1, C119.1, C120.1, C121.1, C186.1, C238.1, IC10.A1 (VDDQ_1), IC10.A8 (VDDQ_2), IC10.B2 (VDD_1), IC10.C1 (VDDQ_3), IC10.C9 (VDDQ_4), IC10.D2 (VDDQ_5), IC10.D9 (VDD_2), IC10.E9 (VDDQ_6), IC10.F1 (VDDQ_7), IC10.G7 (VDD_3), IC10.H2 (VDDQ_8), IC10.H9 (VDDQ_9), IC10.K2 (VDD_4), IC10.K8 (VDD_5), IC10.N1 (VDD_6), IC10.N9 (VDD_7), IC10.R1 (VDD_8), IC10.R9 (VDD_9), R94.1; also elsewhere on the board
/DDR3-2/CK_N: IC10.K7 (CK#), R93.2; also elsewhere on the board
/DDR3-2/CK_P: IC10.J7 (CK), R93.1; also elsewhere on the board
/DDR3-2/DDR301_A0: IC10.N3 (A0); also elsewhere on the board
/DDR3-2/DDR301_A1: IC10.P7 (A1); also elsewhere on the board
/DDR3-2/DDR301_A2: IC10.P3 (A2); also elsewhere on the board
/DDR3-2/DDR301_A3: IC10.N2 (A3); also elsewhere on the board
/DDR3-2/DDR301_A4: IC10.P8 (A4); also elsewhere on the board
/DDR3-2/DDR301_A5: IC10.P2 (A5); also elsewhere on the board
/DDR3-2/DDR301_A6: IC10.R8 (A6); also elsewhere on the board
/DDR3-2/DDR301_A7: IC10.R2 (A7); also elsewhere on the board
/DDR3-2/DDR301_A8: IC10.T8 (A8); also elsewhere on the board
/DDR3-2/DDR301_A9: IC10.R3 (A9); also elsewhere on the board
/DDR3-2/DDR301_A10/AP: IC10.L7 (A10/AP); also elsewhere on the board
/DDR3-2/DDR301_A11: IC10.R7 (A11); also elsewhere on the board
/DDR3-2/DDR301_A12/nBC: IC10.N7 (A12/BC#); also elsewhere on the board
/DDR3-2/DDR301_A13: IC10.T3 (A13); also elsewhere on the board
/DDR3-2/DDR301_A14: IC10.T7 (A14); also elsewhere on the board
/DDR3-2/DDR301_BA0: IC10.M2 (BA0); also elsewhere on the board
/DDR3-2/DDR301_BA1: IC10.N8 (BA1); also elsewhere on the board
/DDR3-2/DDR301_BA2: IC10.M3 (BA2); also elsewhere on the board
/DDR3-2/DDR301_CLKE: IC10.K9 (CKE); also elsewhere on the board
/DDR3-2/DDR301_DQ0: IC10.E3 (DQ0); also elsewhere on the board
/DDR3-2/DDR301_DQ1: IC10.F7 (DQ1); also elsewhere on the board
/DDR3-2/DDR301_DQ2: IC10.F2 (DQ2); also elsewhere on the board
/DDR3-2/DDR301_DQ3: IC10.F8 (DQ3); also elsewhere on the board
/DDR3-2/DDR301_DQ4: IC10.H3 (DQ4); also elsewhere on the board
/DDR3-2/DDR301_DQ5: IC10.H8 (DQ5); also elsewhere on the board
/DDR3-2/DDR301_DQ6: IC10.G2 (DQ6); also elsewhere on the board
/DDR3-2/DDR301_DQ7: IC10.H7 (DQ7); also elsewhere on the board
/DDR3-2/DDR301_DQ8: IC10.D7 (DQ8); also elsewhere on the board
/DDR3-2/DDR301_DQ9: IC10.C3 (DQ9); also elsewhere on the board
/DDR3-2/DDR301_DQ10: IC10.C8 (DQ10); also elsewhere on the board
/DDR3-2/DDR301_DQ11: IC10.C2 (DQ11); also elsewhere on the board
/DDR3-2/DDR301_DQ12: IC10.A7 (DQ12); also elsewhere on the board
/DDR3-2/DDR301_DQ13: IC10.A2 (DQ13); also elsewhere on the board
/DDR3-2/DDR301_DQ14: IC10.B8 (DQ14); also elsewhere on the board
/DDR3-2/DDR301_DQ15: IC10.A3 (DQ15); also elsewhere on the board
/DDR3-2/DDR301_LDM: IC10.E7 (LDM); also elsewhere on the board
/DDR3-2/DDR301_LDQS_N: IC10.G3 (LDQS#); also elsewhere on the board
/DDR3-2/DDR301_LDQS_P: IC10.F3 (LDQS); also elsewhere on the board
/DDR3-2/DDR301_ODT: IC10.K1 (ODT); also elsewhere on the board
/DDR3-2/DDR301_UDM: IC10.D3 (UDM); also elsewhere on the board
/DDR3-2/DDR301_UDQS_N: IC10.B7 (UDQS#); also elsewhere on the board
/DDR3-2/DDR301_UDQS_P: IC10.C7 (UDQS); also elsewhere on the board
/DDR3-2/DDR301_nCAS: IC10.K3 (CAS#), R92.1; also elsewhere on the board
/DDR3-2/DDR301_nCS: IC10.L2 (CS#); also elsewhere on the board
/DDR3-2/DDR301_nRAS: IC10.J3 (RAS#); also elsewhere on the board
/DDR3-2/DDR301_nRST: IC10.T2 (RESET#), R91.1; also elsewhere on the board
/DDR3-2/DDR301_nWE: IC10.L3 (WE#); also elsewhere on the board
/DDR3-2/VREF_DDR3: C99.1, C100.1, C107.1, IC10.H1 (VREFDQ), IC10.M8 (VREFCA), R94.2, R95.1
GND: C99.2, C100.2, C101.2, C102.2, C103.2, C104.2, C105.2, C106.2, C107.2, C108.2, C109.2, C110.2, C111.2, C112.2, C113.2, C114.2, C115.2, C116.2, C117.2, C118.2, C119.2, C120.2, C121.2, C186.2, C238.2, IC10.A9 (VSS_1), IC10.B1 (VSSQ_1), IC10.B3 (VSS_2), IC10.B9 (VSSQ_2), IC10.D1 (VSSQ_3), IC10.D8 (VSSQ_4), IC10.E1 (VSS_3), IC10.E2 (VSSQ_5), IC10.E8 (VSSQ_6), IC10.F9 (VSSQ_7), IC10.G1 (VSSQ_8), IC10.G8 (VSS_4), IC10.G9 (VSSQ_9), IC10.J2 (VSS_5), IC10.J8 (VSS_6), IC10.M1 (VSS_7), IC10.M9 (VSS_8), IC10.P1 (VSS_9), IC10.P9 (VSS_10), IC10.T1 (VSS_11), IC10.T9 (VSS_12), R90.2, R91.2, R92.2, R95.2; also elsewhere on the board
unnamed: IC10.L8 (ZQ), R90.1

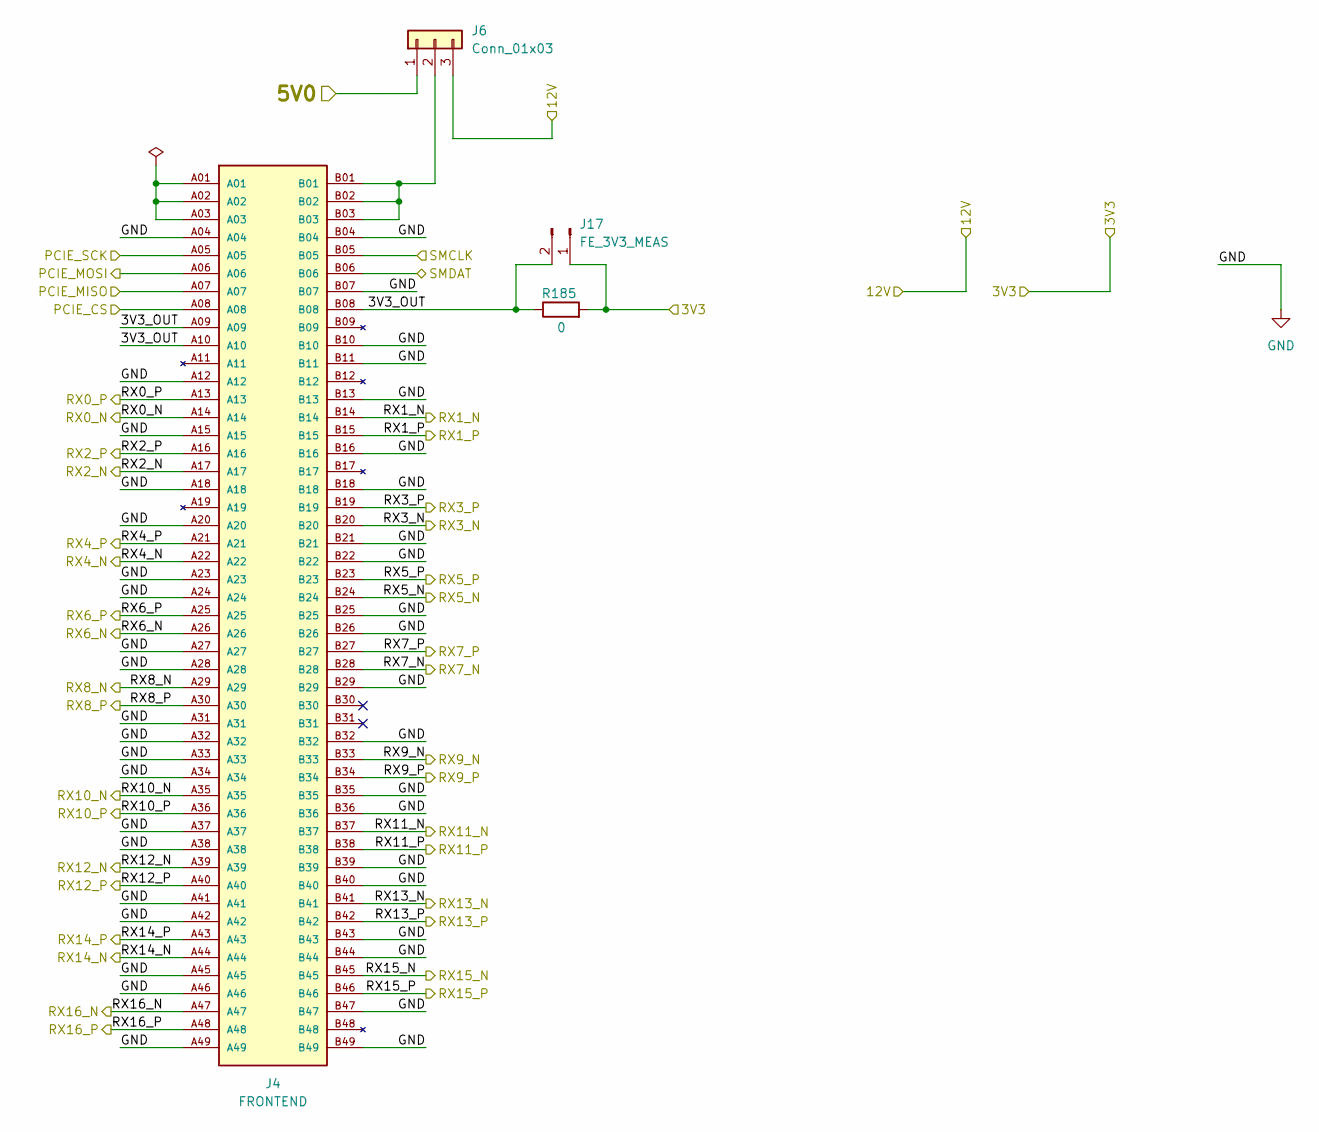
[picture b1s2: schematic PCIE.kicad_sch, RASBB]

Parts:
J4: FRONTEND; SAMTEC_PCIE-098-02-X-D-EMS3; Mfr. Part # X3157WS-98-9TV30; LCSC Part # C5711253
J6: Conn_01x03; PinHeader_1x03_P2.54mm_Vertical; Mfr. Part # PZ254V-11-03P; LCSC Part # C2937625
J17: FE_3V3_MEAS; PinHeader_1x02_P2.54mm_Vertical; Mfr. Part # PZ254V-11-02P; LCSC Part # C492401
R185: 0; R_1206_3216Metric; Mfr. Part # 1206W4F0000T5E; LCSC Part # C17888

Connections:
/Audio_IN-OUT/3V3: J17.1, R185.2; also elsewhere on the board
/Audio_IN-OUT/5V0: J6.1; also elsewhere on the board
/PCIE/3V3_OUT: J4.A09, J4.A10, J4.B08, J17.2, R185.1
/PCIE/12V: J6.3; also elsewhere on the board
/PCIE/PCIE_CS: J4.A08; also elsewhere on the board
/PCIE/PCIE_MISO: J4.A07; also elsewhere on the board
/PCIE/PCIE_MOSI: J4.A06; also elsewhere on the board
/PCIE/PCIE_SCK: J4.A05; also elsewhere on the board
/PCIE/RX0_N: J4.A14; also elsewhere on the board
/PCIE/RX0_P: J4.A13; also elsewhere on the board
/PCIE/RX1_N: J4.B14; also elsewhere on the board
/PCIE/RX1_P: J4.B15; also elsewhere on the board
/PCIE/RX2_N: J4.A17; also elsewhere on the board
/PCIE/RX2_P: J4.A16; also elsewhere on the board
/PCIE/RX3_N: J4.B20; also elsewhere on the board
/PCIE/RX3_P: J4.B19; also elsewhere on the board
/PCIE/RX4_N: J4.A22; also elsewhere on the board
/PCIE/RX4_P: J4.A21; also elsewhere on the board
/PCIE/RX5_N: J4.B24; also elsewhere on the board
/PCIE/RX5_P: J4.B23; also elsewhere on the board
/PCIE/RX6_N: J4.A26; also elsewhere on the board
/PCIE/RX6_P: J4.A25; also elsewhere on the board
/PCIE/RX7_N: J4.B28; also elsewhere on the board
/PCIE/RX7_P: J4.B27; also elsewhere on the board
/PCIE/RX8_N: J4.A29; also elsewhere on the board
/PCIE/RX8_P: J4.A30; also elsewhere on the board
/PCIE/RX9_N: J4.B33; also elsewhere on the board
/PCIE/RX9_P: J4.B34; also elsewhere on the board
/PCIE/RX10_N: J4.A35; also elsewhere on the board
/PCIE/RX10_P: J4.A36; also elsewhere on the board
/PCIE/RX11_N: J4.B37; also elsewhere on the board
/PCIE/RX11_P: J4.B38; also elsewhere on the board
/PCIE/RX12_N: J4.A39; also elsewhere on the board
/PCIE/RX12_P: J4.A40; also elsewhere on the board
/PCIE/RX13_N: J4.B41; also elsewhere on the board
/PCIE/RX13_P: J4.B42; also elsewhere on the board
/PCIE/RX14_N: J4.A44; also elsewhere on the board
/PCIE/RX14_P: J4.A43; also elsewhere on the board
/PCIE/RX15_N: J4.B45; also elsewhere on the board
/PCIE/RX15_P: J4.B46; also elsewhere on the board
/PCIE/RX16_N: J4.A47; also elsewhere on the board
/PCIE/RX16_P: J4.A48; also elsewhere on the board
/PCIE/SMCLK: J4.B05; also elsewhere on the board
/PCIE/SMDAT: J4.B06; also elsewhere on the board
GND: J4.A04, J4.A12, J4.A15, J4.A18, J4.A20, J4.A23, J4.A24, J4.A27, J4.A28, J4.A31, J4.A32, J4.A33, J4.A34, J4.A37, J4.A38, J4.A41, J4.A42, J4.A45, J4.A46, J4.A49, J4.B04, J4.B07, J4.B10, J4.B11, J4.B13, J4.B16, J4.B18, J4.B21, J4.B22, J4.B25, J4.B26, J4.B29, J4.B32, J4.B35, J4.B36, J4.B39, J4.B40, J4.B43, J4.B44, J4.B47, J4.B49; also elsewhere on the board
unnamed: J4.A01, J4.A02, J4.A03
unnamed: J4.B01, J4.B02, J4.B03, J6.2

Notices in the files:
OWIFI_RX/boards/rasbb_rasrf/rasbb_rasrf.xdc:
SPDX-FileCopyrightText: 2026 Tobias Weber
SPDX-License-Identifier: GPL-3.0-only
RASBB/Hardware/Rev.C/Design/RASBB.kicad_pcb:
Licensed under CERN-OHL-S-2.0
RASRF_2400WB/Hardware/PCB_Design/ADC3221.kicad_sch:
GNU GENERAL PUBLIC LICENSE Version 2, June 1991
